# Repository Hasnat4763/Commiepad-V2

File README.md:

# Commiepad V2

A fully custom designed macro pad.
It is a sequel to my 1st macropad design [Commiepad](https://github.com/Hasnat4763/CommiePad). The 1st one was not working fully as I had made some mistakes in the PCB by not using a matrix and combining OLED SDA with neopixel data line. So I fixed that mistake in this one. It can be used for running macros which can help people like programmers and designers to run commands they need to run a lot just by clicking one key instead of multiple.

# Motivation

As my 1st hackpad design didn't work, and I had some free time, I thought of designing a new hackpad.

## Parts used:  
- SEEED XIAO RP 2040 with custom KMK firmware 
- 8 Cherry MX switches
- EC 11 encoder
- SSD1306 OLED
- Custom desktop app to control underglow and OLED

## Gallery

# PCB

Schematic

PCB

PCB Rendered

# CAD

Full Board Assembled

Bottom Part

Top Cover

# Zine Poster

# BOM

| Item                                             | Quantity | Price          | Link |
|--------------------------------------------------|----------|----------------|------|
| SEEED XIAO RP2040 (THT)                          | 1        | $$7.25          | [Link](https://www.seeedstudio.com/XIAO-RP2040-v1-0-p-5026.html) |
| Outemu Silent Peach V3 Switch                              | 10      | $6.09          | [Link](https://www.aliexpress.com/item/1005006905361113.html) |
| SK6812-MINI-E (RGB LEDs)                         | 20      | $5.26         | [Link](https://www.aliexpress.com/item/1005005193716172.html) |
| 1N4148 Diode                                     | 100      | $1.20          | [Link](https://www.aliexpress.com/item/4000142272546.html) |
| SSD1306 OLED Display                             | 1        | $5.15           | [Link](https://www.aliexpress.com/item/1005008640132638.html) |
| YMDK Blank DSA 1u Keycap                         | 10       | $6.43          | [Link](https://www.aliexpress.com/item/32842379355.html) |
| EC 11 Encoder with Push Button Half Handle 20MM Shaft | 5 | $6.31 | [Link](https://www.aliexpress.com/item/1005005983134515.html) |
| M3 Heat Set Inserts | 30 | $6.13 | [Link](https://www.aliexpress.com/item/1005006071488810.html) |
| M3 Fasteners | 50 | $6.28 | [Link](https://www.aliexpress.com/item/1005011845940916.html) |
| Top Case                                         | 1        | Printing Legion |  |
| Bottom Case                                      | 1        | Printing Legion |  |
| PCB | 5 | $11.02 | JLCPCB |

## Build and Use

# Where to get the PCB

To fabricate the PCB, use any PCB fabricators you can find for cheap, for most people it's JLCPCB. But then you also have to check the shipping cost and customs of your country.
For the parts, aliexpress works. But then you can also get them from your local suppliers too.

# Flashing the firmware

First, follow the [KMK starter guide](https://github.com/KMKfw/kmk_firmware/blob/main/docs/en/Getting_Started.md) to flash KMK on your microcontroller, My repository already has the KMK files necessary with all the extra libraries for the SSD1306 OLED, so you can follow the KMK starter guide but remember to copy the files from this repository instead of the KMK one. Remember to copy the [serialcommand.py](https://github.com/Hasnat4763/Commiepad-V2/blob/c52ac5da764008b54e5d9a0160083da586aadd7f/Commiepad%20V2%20Firmware%20KMK/serialcommand.py) else you won't be able to use the desktop app to control the RGB underglow. You can change the keys you want the macro pad to press on the [main.py](https://github.com/Hasnat4763/Commiepad-V2/blob/aac4e51710a858434e91d4a1d5ed2a7157012af6/Commiepad%20V2%20Firmware%20KMK/main.py), as I have just put some placeholder keys like A, B, C, D etc. for now. You may even make layers so one key can be used to trigger multiple keys!

# Using the desktop app

the desktop app looks like this 

I have included a build for windows [here](Software/CommiepadV2.exe)

To build for Mac/Linux:

```
# 1. Create virtual environment
python3 -m venv commiepad_env
source commiepad_env/bin/activate

# 2. Install dependencies
pip install -r requirements.txt

# 3. Build executable
pyinstaller --onefile --windowed --add-data "main.ui:." --add-data "bg.png:." --hidden-import=PyQt6.QtCore --hidden-import=PyQt6.QtGui --hidden-import=PyQt6.QtWidgets --hidden-import=PyQt6.uic --name CommiepadV2 main.py

```

After launching the app, select the COM port your Macropad is connected to, and select the baud rate (Most popular option is 115200), after that click the button called "Start Connection". After successful connection, the debug area will show a message about it. Then you can start controlling the RGB and also put text on the OLED from it.

Features of this app:
- Can turn underglow on/off
- Set custom color to it
- Set RGB mode to KMK presets
- Set any text to the OLED

I may add some more features to it later. For now these should work (They haven't been tested yet).

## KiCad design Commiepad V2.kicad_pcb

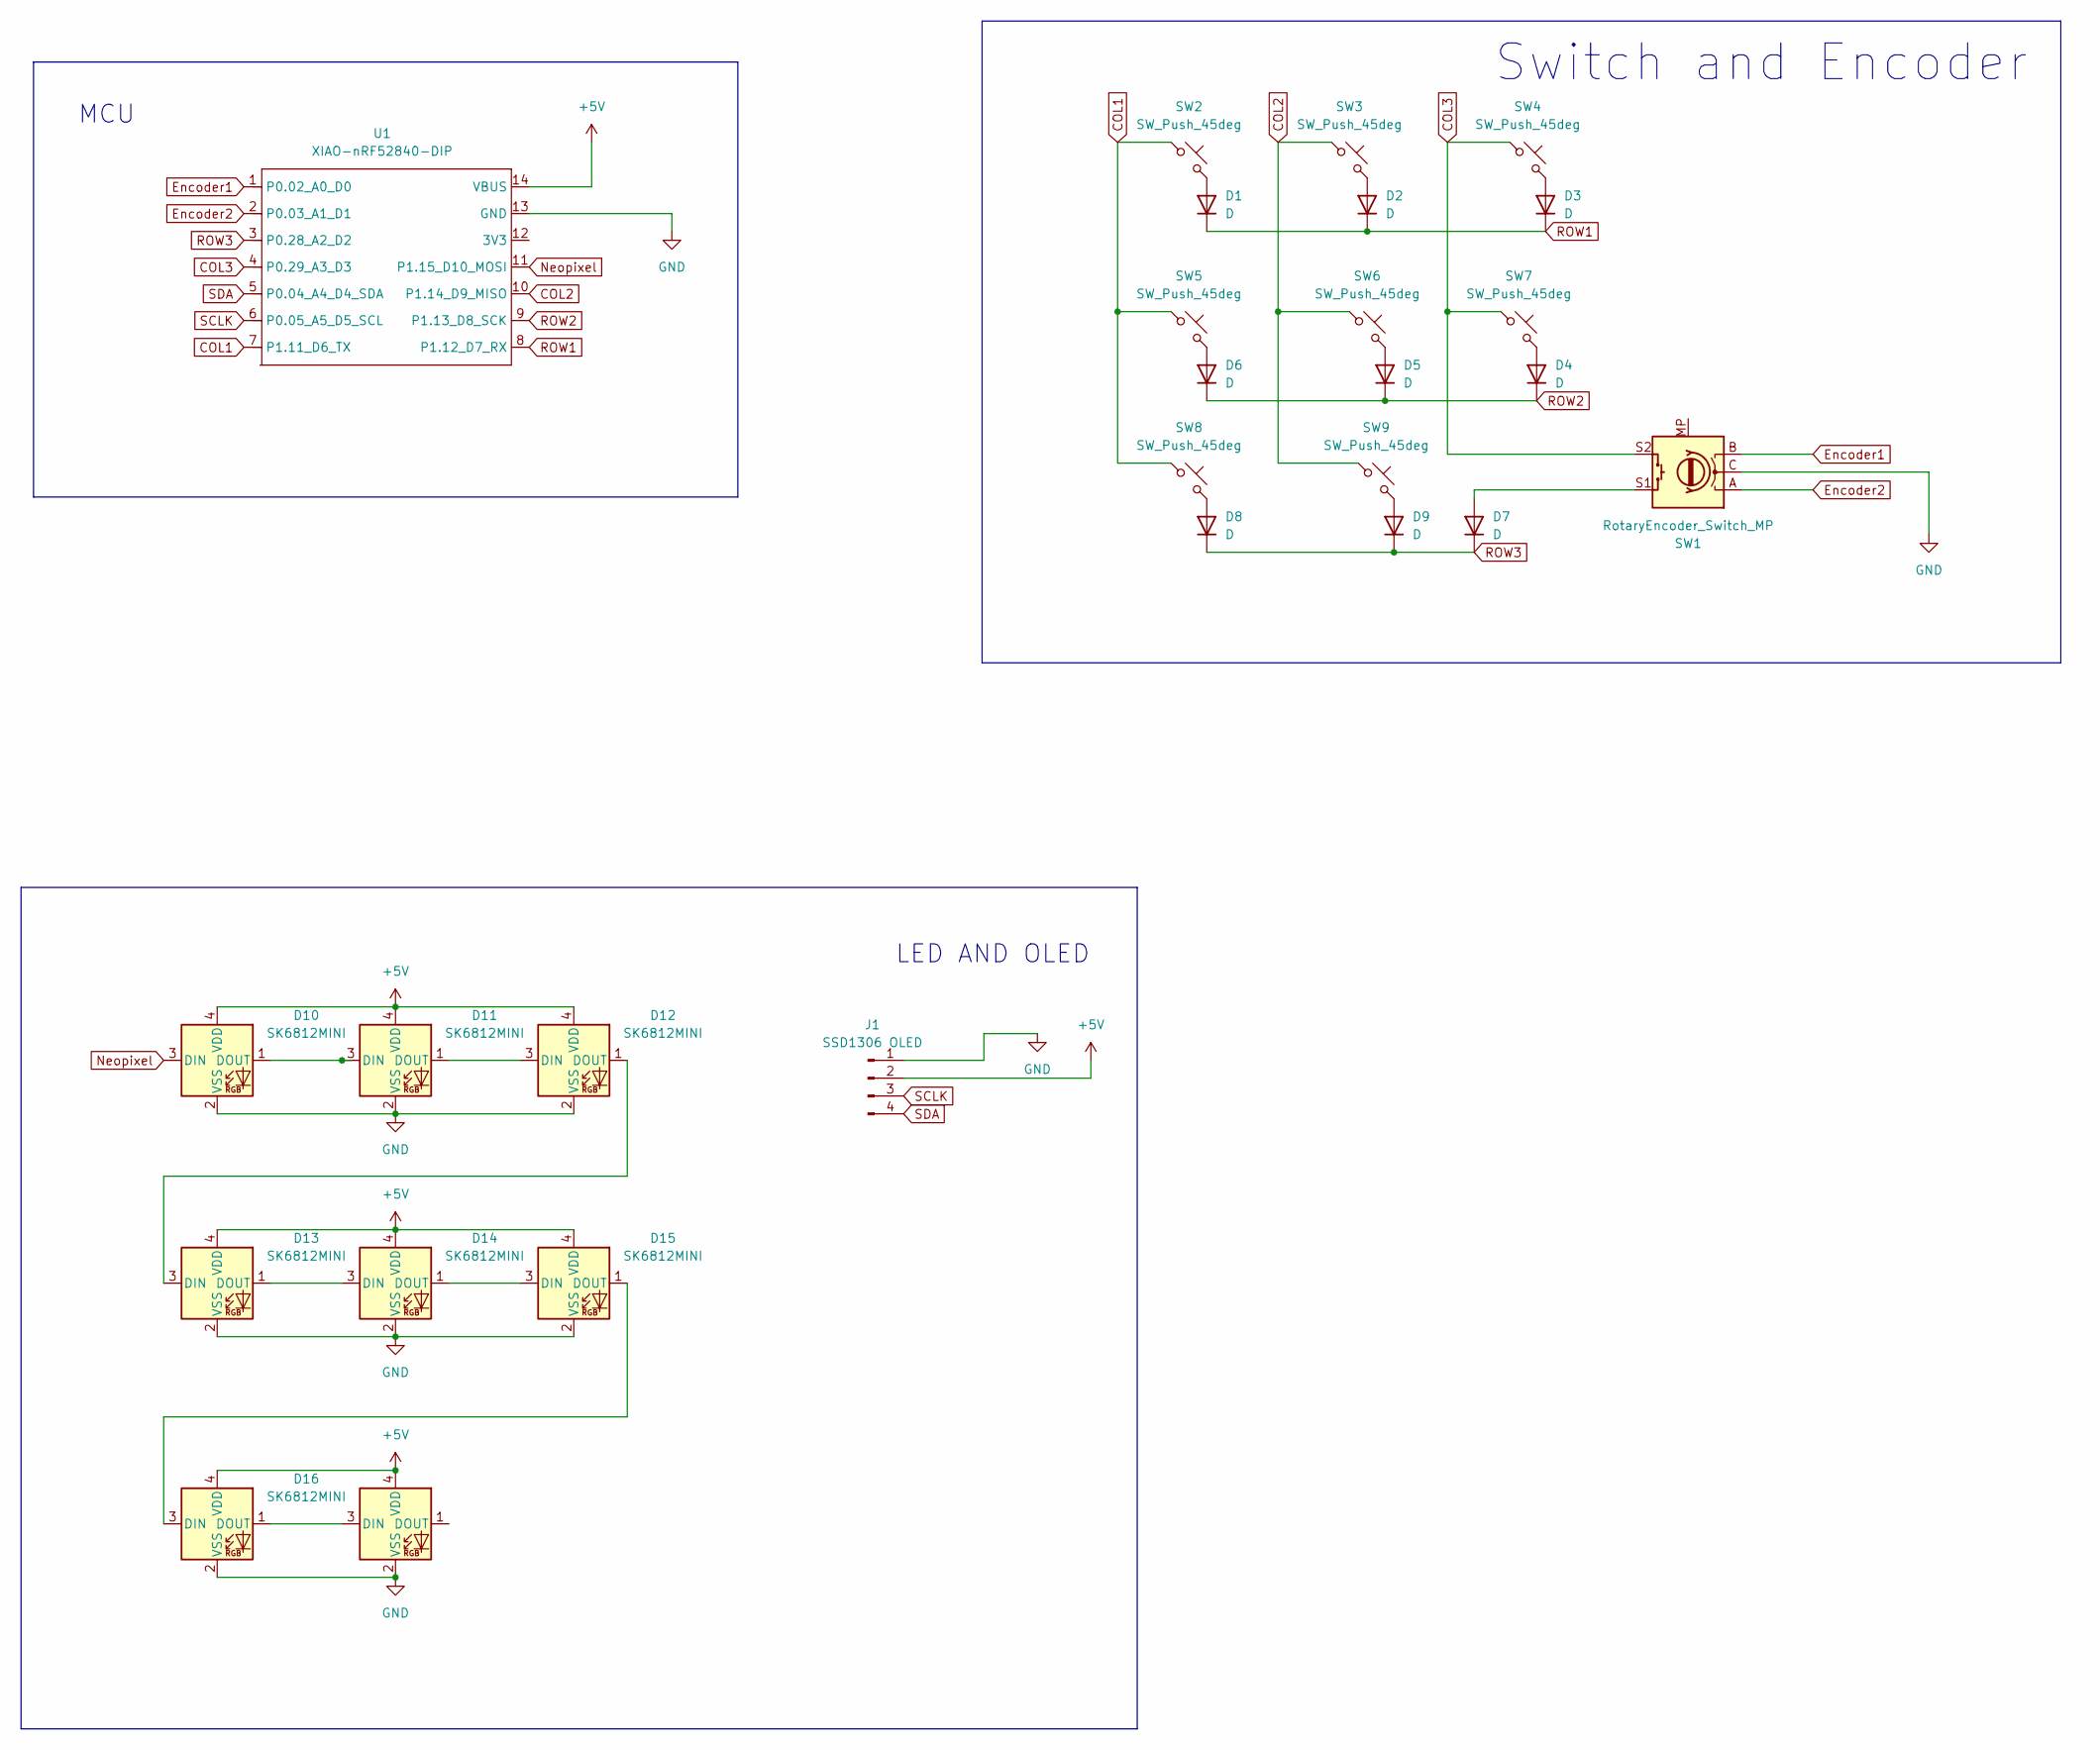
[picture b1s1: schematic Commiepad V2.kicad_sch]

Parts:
D1, D2, D3, D4, D5, D6, D7, D8, D9: D; D_DO-41_SOD81_P7.62mm_Horizontal
D10, D11, D12, D13, D14, D15, D16, D17: SK6812MINI; SK6812-MINI-E
J1: SSD1306 OLED; SSD1306-0.91-OLED-4pin-128x32
SW1: RotaryEncoder_Switch_MP; RotaryEncoder_Alps_EC11E-Switch_Vertical_H20mm
SW2, SW3, SW4, SW5, SW6, SW7, SW8, SW9: SW_Push_45deg; SW_Cherry_MX_1.00u_PCB
U1: XIAO-nRF52840-DIP

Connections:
+5V: D10.4 (VDD), D11.4 (VDD), D12.4 (VDD), D13.4 (VDD), D14.4 (VDD), D15.4 (VDD), D16.4 (VDD), D17.4 (VDD), J1.2, U1.14 (VBUS)
COL1: SW2.1, SW5.1, SW8.1, U1.7 (GPIO0/TX)
COL2: SW3.1, SW6.1, SW9.1, U1.10 (GPIO4/MISO)
COL3: SW1.S2, SW4.1, SW7.1, U1.4 (GPIO29/ADC3/A3)
Encoder1: SW1.B, U1.1 (GPIO26/ADC0/A0)
Encoder2: SW1.A, U1.2 (GPIO27/ADC1/A1)
GND: D10.2 (VSS), D11.2 (VSS), D12.2 (VSS), D13.2 (VSS), D14.2 (VSS), D15.2 (VSS), D16.2 (VSS), D17.2 (VSS), J1.1, SW1.C, U1.13 (GND)
Neopixel: D10.3 (DIN), U1.11 (GPIO3/MOSI)
unnamed: D1.2 (A), SW2.2
unnamed: D2.2 (A), SW3.2
unnamed: D3.2 (A), SW4.2
unnamed: D4.2 (A), SW7.2
unnamed: D5.2 (A), SW6.2
unnamed: D6.2 (A), SW5.2
unnamed: D7.2 (A), SW1.S1
unnamed: D8.2 (A), SW8.2
unnamed: D9.2 (A), SW9.2
unnamed: D10.1 (DOUT), D11.3 (DIN)
unnamed: D11.1 (DOUT), D12.3 (DIN)
unnamed: D12.1 (DOUT), D13.3 (DIN)
unnamed: D13.1 (DOUT), D14.3 (DIN)
unnamed: D14.1 (DOUT), D15.3 (DIN)
unnamed: D15.1 (DOUT), D16.3 (DIN)
unnamed: D16.1 (DOUT), D17.3 (DIN)
ROW1: D1.1 (K), D2.1 (K), D3.1 (K), U1.8 (GPIO1/RX)
ROW2: D4.1 (K), D5.1 (K), D6.1 (K), U1.9 (GPIO2/SCK)
ROW3: D7.1 (K), D8.1 (K), D9.1 (K), U1.3 (GPIO28/ADC2/A2)
SCLK: J1.3, U1.6 (GPIO7/SCL)
SDA: J1.4, U1.5 (GPIO6/SDA)

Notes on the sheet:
Switch and Encoder
LED AND OLED
MCU

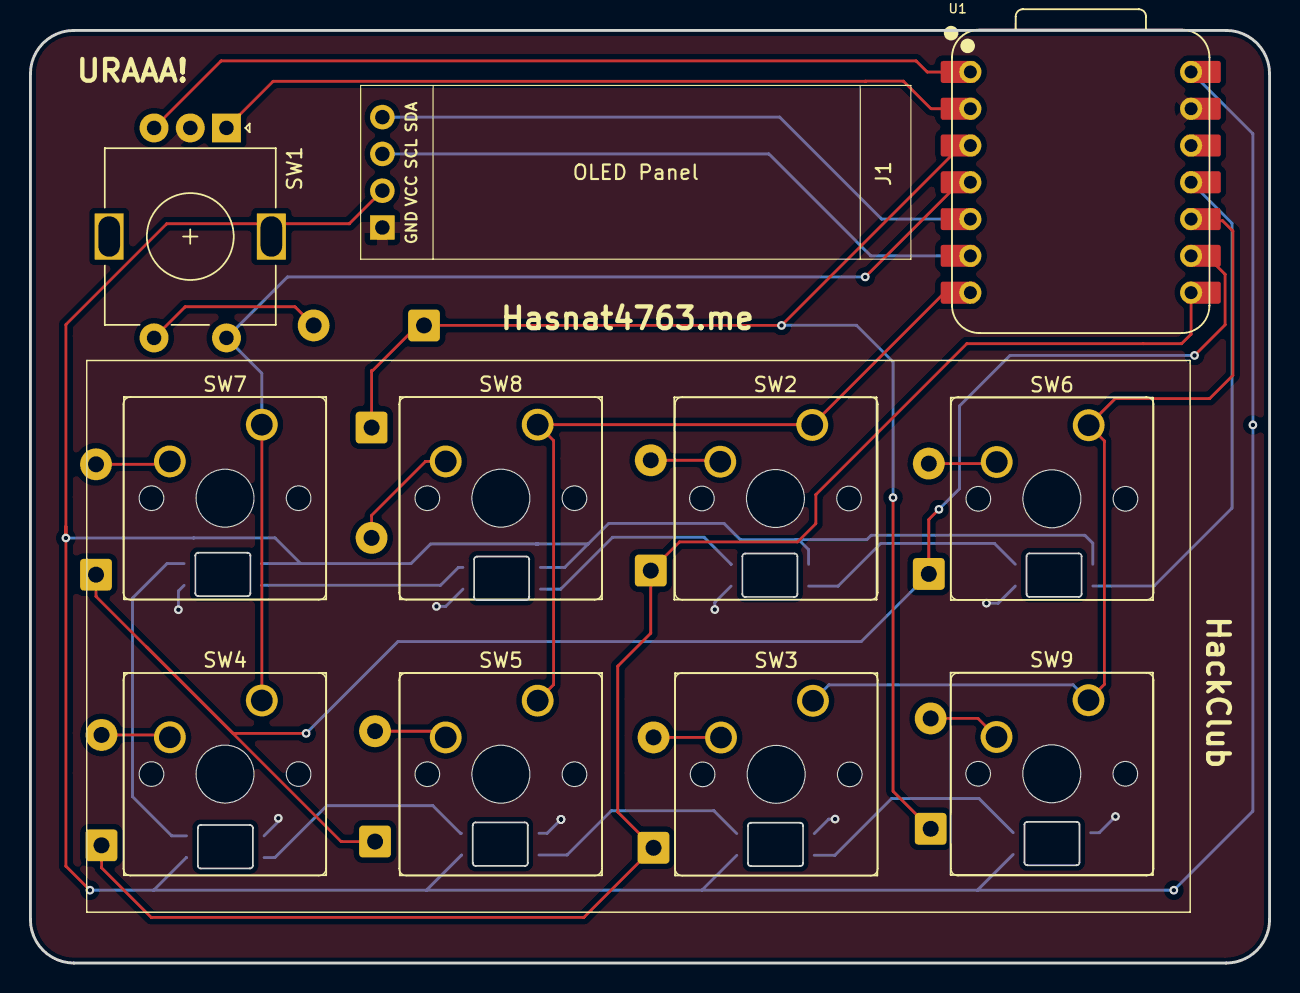
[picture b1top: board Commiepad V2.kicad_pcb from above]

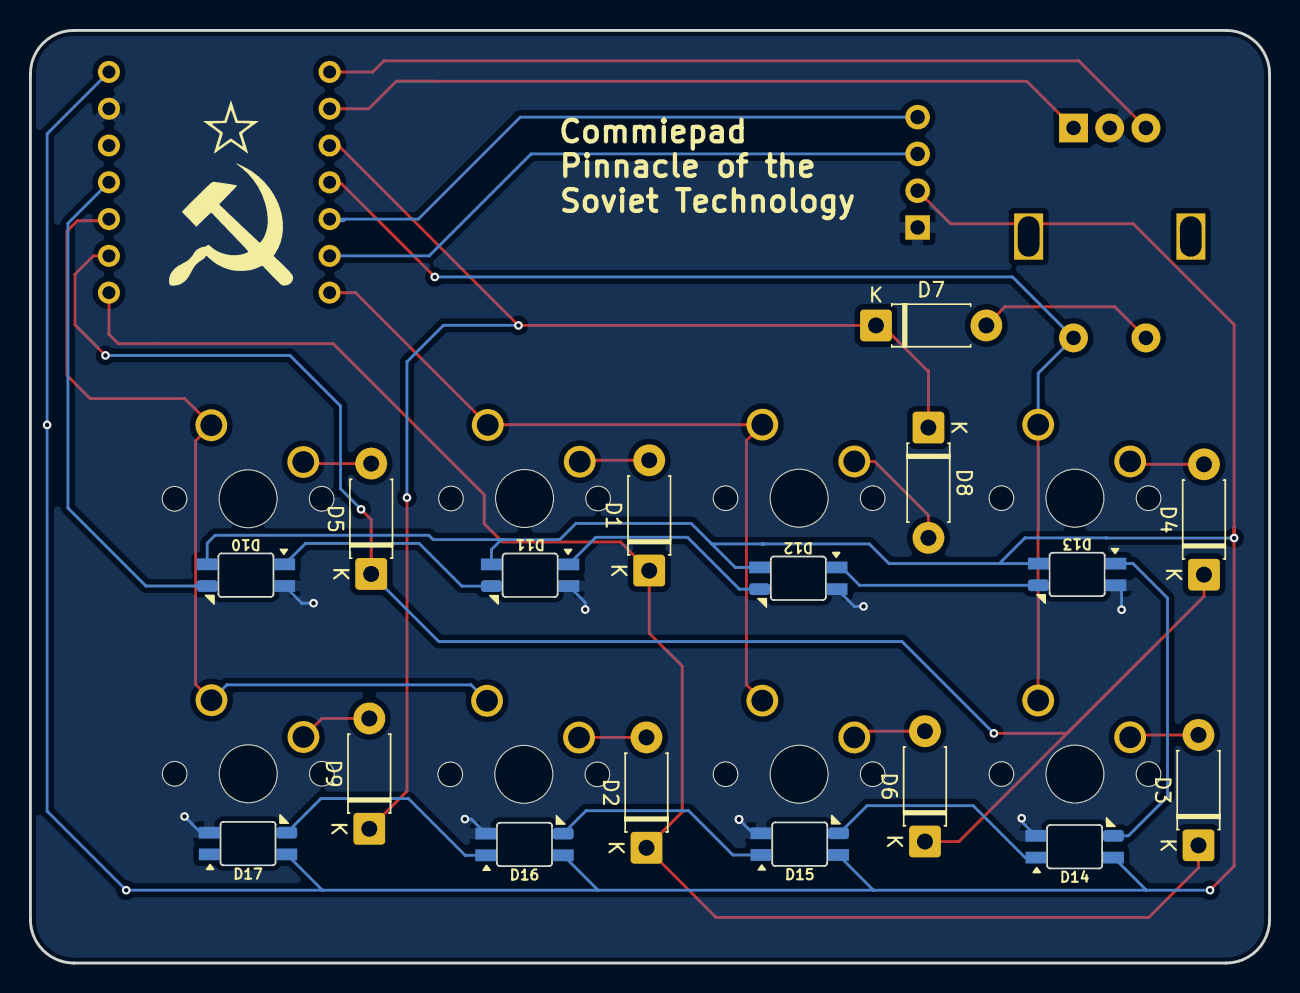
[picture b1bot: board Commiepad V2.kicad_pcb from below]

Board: 2 copper layers, 85.6 x 64.4 mm, 28 parts (17 on the bottom side), 29 nets.

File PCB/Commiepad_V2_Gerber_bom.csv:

Designator,Footprint,Quantity,Value,LCSC Part #
"D1, D2, D3, D4, D5, D6, D7, D8, D9",D_DO-41_SOD81_P7.62mm_Horizontal,9,D,
"D10, D11, D12, D13, D14, D15, D16, D17",SK6812-MINI-E,8,SK6812MINI,
J1,SSD1306-0.91-OLED-4pin-128x32,1,SSD1306 OLED,
SW1,RotaryEncoder_Alps_EC11E-Switch_Vertical_H20mm,1,RotaryEncoder_Switch_MP,
"SW2, SW3, SW4, SW5, SW6, SW7, SW8, SW9",SW_Cherry_MX_1.00u_PCB,8,SW_Push_45deg,
U1,XIAO-RP2040-DIP,1,XIAO-RP2040-DIP,

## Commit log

2026-04-09 Schematic Done
2026-04-30 Changed the MCU to nRF52840 for wireless connectivity
2026-05-16 Had to re add everything T_T
2026-05-16 Moved the PCB source files to a different folder
2026-05-16 Updated and fixed sum bugs on the desktop app
2026-05-16 Added JSON parsing to the firmware as a kmk extension which can be reused for later easily
2026-05-17 Added PCB, CAD files and edited the README
2026-05-17 changed pcb-render to pcb_render
2026-05-17 Trying out Markdown table for BOM
2026-05-17 Adding more info to README.md including BOM
2026-05-17 did some more changes
2026-05-17 Fixing one readme bug
2026-05-17 Finishing touch ig
2026-05-17 Updated BOM with new prices and links for components.
2026-05-17 tidying up by adding a folder for images
2026-05-17 combined the app to one executable for windows
2026-05-17 Add instruction to build linux/mac version of app with renaming bom.csv to BOM.csv
2026-05-17 add BOM.csv
2026-05-17 Added bom.csv with gerber extra csvs
2026-05-17 Added links to bom
2026-05-22 Adding M3 Heat Set Insert and Fasteners to BOM
2026-05-22 Add M3 Heat Set Inserts and M3 Fasteners to BOM
2026-05-26 update readme with motivation
